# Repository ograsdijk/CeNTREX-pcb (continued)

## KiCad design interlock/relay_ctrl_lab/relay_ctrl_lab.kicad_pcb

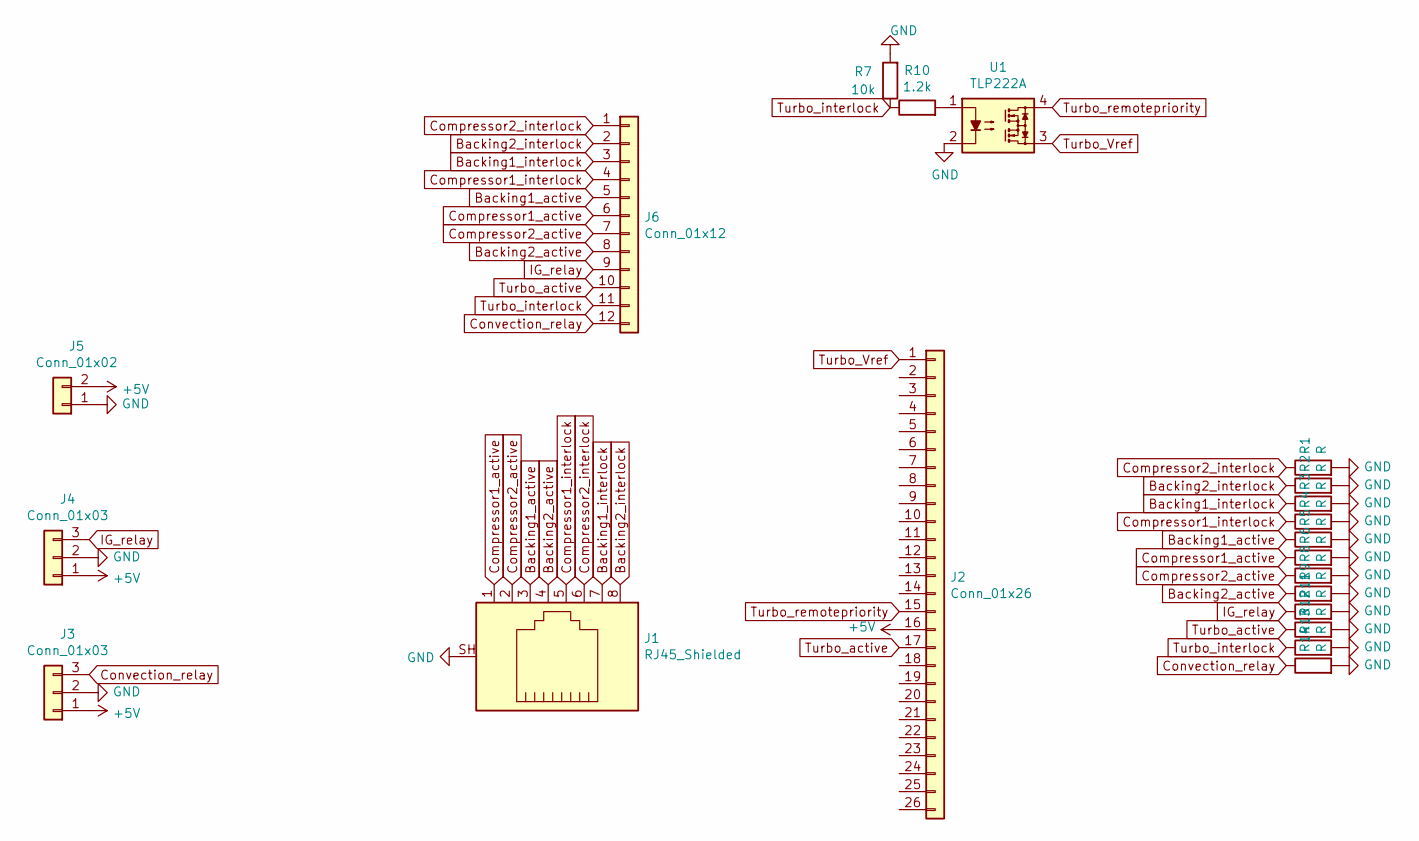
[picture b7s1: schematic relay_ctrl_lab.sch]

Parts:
J1: RJ45_Shielded; RJ45_Amphenol_RJHSE5380
J2: Conn_01x26; DSUB-26-HD_Male_Horizontal_P2.29x1.98mm_EdgePinOffset3.03mm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
J3, J4: Conn_01x03; PinHeader_1x03_P2.54mm_Vertical
J5: Conn_01x02; PinHeader_1x02_P2.54mm_Vertical
J6: Conn_01x12; PinHeader_1x12_P2.54mm_Vertical
R1, R2, R3, R4, R5, R6, R8, R9, R11, R12, R13, R14: R; R_Axial_DIN0204_L3.6mm_D1.6mm_P5.08mm_Horizontal
R7: 10k; R_Axial_DIN0204_L3.6mm_D1.6mm_P5.08mm_Horizontal
R10: 1.2k; R_Axial_DIN0204_L3.6mm_D1.6mm_P5.08mm_Horizontal
U1: TLP222A; DIP-4_W7.62mm

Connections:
+5V: J2.16, J3.1, J4.1, J5.2
Backing1_active: J1.3, J6.5, R5.1
Backing1_interlock: J1.7, J6.3, R3.1
Backing2_active: J1.4, J6.8, R9.1
Backing2_interlock: J1.8, J6.2, R2.1
Compressor1_active: J1.1, J6.6, R6.1
Compressor1_interlock: J1.5, J6.4, R4.1
Compressor2_active: J1.2, J6.7, R8.1
Compressor2_interlock: J1.6, J6.1, R1.1
Convection_relay: J3.3, J6.12, R14.1
GND: J1.SH, J3.2, J4.2, J5.1, R1.2, R2.2, R3.2, R4.2, R5.2, R6.2, R7.2, R8.2, R9.2, R11.2, R12.2, R13.2, R14.2, U1.2
IG_relay: J4.3, J6.9, R11.1
unnamed: R10.2, U1.1
Turbo_Vref: J2.1, U1.3
Turbo_active: J2.17, J6.10, R12.1
Turbo_interlock: J6.11, R7.1, R10.1, R13.1
Turbo_remotepriority: J2.15, U1.4

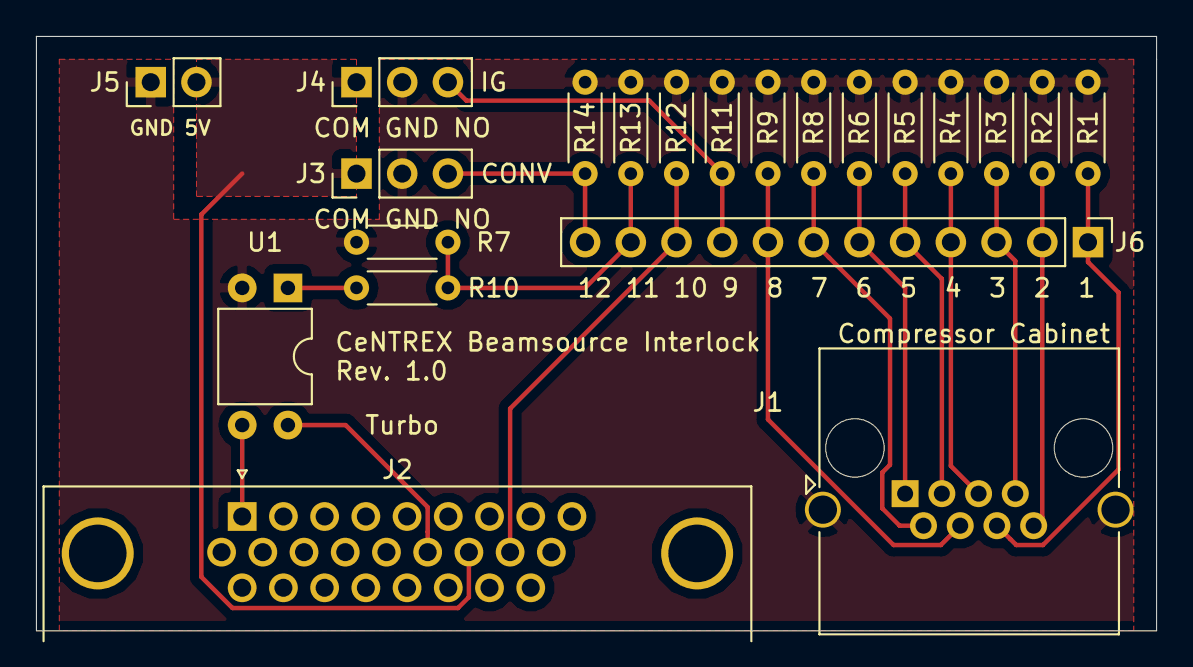
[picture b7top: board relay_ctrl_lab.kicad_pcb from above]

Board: 2 copper layers, 62.2 x 33.0 mm, 21 parts (0 on the bottom side), 17 nets.
